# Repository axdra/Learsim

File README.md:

# Collection of Learsim code

## Glass cockpit displays

- **[`learsim-glass`](learsim-glass/)** — kiosk display app that hosts
  [glassout](https://glassout.flyingart.dev) views (and local standby/clock
  views) fullscreen. Runs headless on a Raspberry Pi and on Windows/macOS. One
  screen config per monitor, so two monitors on one Pi get two independent
  configs.
- **[`learsim-glass-admin`](learsim-glass-admin/)** — desktop app to configure,
  over the LAN, which view each glass screen shows.
- **[`learsim-glass-native`](learsim-glass-native/)** — a native (no-webview)
  display client that renders glassout panels directly via SDL2/KMSDRM. Much
  lighter on a Raspberry Pi than the webview build (no browser engine, no
  compositor) and speaks the same control API, so the admin manages it the same.

See each app's README for architecture, build, and headless-Pi setup.

## Other

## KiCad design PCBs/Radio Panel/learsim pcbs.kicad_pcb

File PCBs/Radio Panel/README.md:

# Learsim Radio Panel — PCB

KiCad project (`learsim pcbs.kicad_*`) for the Learsim flight-sim **COM/NAV radio
panel**: an ESP32-C6 drives two MAX7219 LED drivers that multiplex two 6-digit
7-segment displays, plus two rotary encoders, six mode buttons with per-button
SK6812 RGB backlights, two indicator LEDs and an SPDT toggle.

## Block diagram

```
         USB-C 5V ── Vbus ─┬─ ESP32-C6 (Vsys)
                           ├─ MAX7219 U2/U3  V+
                           └─ SK6812 D1..D6  VDD
 ESP32-C6 (U1)
   GPIO6  ── SPI DIN ─▶ U2.DIN ─▶ U2.DOUT ─▶ U3.DIN     (daisy-chain)
   GPIO7  ── SPI CLK ─▶ U2.CLK, U3.CLK
   GPIO4  ── SPI LOAD▶ U2.LOAD, U3.LOAD
   GPIO21 ── LED DATA▶ D5 ▶ D1 ▶ D2 ▶ D3 ▶ D4 ▶ D6      (WS2812-style chain)
   GPIO15/16/5  ── Encoder SW1 (MHz)  A / B / push
   GPIO18/19/20 ── Encoder SW2 (KHz)  A / B / push
   GPIO2/0/1/14 ── COM1 COM2 NAV1 Switch1 buttons
   EXIO2 / EXIO3 (TCA9554) ── NAV2 / ADF1 buttons
   GPIO3 / GPIO17 ── COM1 / COM2 indicator LEDs (D7 / D8)
   EXIO6 / EXIO7 (TCA9554) ── SW3 toggle throws A / B

   U2 ─▶ DS2 (6-digit display)      U3 ─▶ DS1 (6-digit display)
```

## ESP32-C6 GPIO map

| Function            | ESP32-C6 pin   | Net       |
|---------------------|----------------|-----------|
| MAX7219 SPI DIN     | GPIO6          | SPI_DIN   |
| MAX7219 SPI CLK     | GPIO7          | SPI_CLK   |
| MAX7219 SPI LOAD/CS | GPIO4          | SPI_LOAD  |
| SK6812 data out     | GPIO21         | LED_DIN   |
| Encoder MHz A / B   | GPIO15 / GPIO16 (TX) | ENC1_A/B |
| Encoder MHz push    | GPIO5          | ENC1_SW   |
| Encoder KHz A / B   | GPIO18 / GPIO19 | ENC2_A/B |
| Encoder KHz push    | GPIO20         | ENC2_SW   |
| COM1 button         | GPIO2          | BTN_COM1  |
| COM2 button         | GPIO0          | BTN_COM2  |
| NAV1 button         | GPIO1          | BTN_NAV1  |
| NAV2 button         | EXIO2 (TCA9554)| BTN_NAV2  |
| ADF1 button         | EXIO3 (TCA9554)| BTN_ADF1  |
| Switch1 button      | GPIO14         | BTN_Switch1 |
| COM1 indicator LED  | GPIO3          | COM1_LED  |
| COM2 indicator LED  | GPIO17 (RX)    | COM2_LED  |
| SW3 toggle throw 1  | EXIO6 (TCA9554)| SW3_A     |
| SW3 toggle throw 2  | EXIO7 (TCA9554)| SW3_B     |
| Power in            | USB-C (Vbus)   | +5V       |
| Logic rail          | 3V3            | +3V3      |

Spare pins for expansion: **GPIO8, GPIO9, EXIO1, EXIO4, EXIO5**. Note GPIO8/GPIO9
are ESP32-C6 strapping/boot pins (GPIO9 low at reset selects download mode) — only
attach loads there that are guaranteed high-or-floating at reset (GPIO8 also drives
the module's onboard RGB LED). **GPIO22/GPIO23 are NOT spare**: they are the I2C
bus (SDA/SCL) to the module's onboard TCA9554 expander that reads the NAV2/ADF1
buttons and SW3 — leave them unconnected; only I2C slaves may ever attach there.

**Encoder MHz B is on the TX pin (GPIO16) and the COM2 LED on RX (GPIO17)**, so
the UART0 serial console is not available; use the ESP32-C6's native USB for
flashing/logs. The ROM bootloader drives TX briefly at reset — harmless for the
encoder, but expect a short glitch on ENC1_B during boot.

**SW3 (SPDT toggle, 2MD1T1B1M2QES-5).** Common pole (pin 2) → GND; each throw read
with a 10 kΩ pull-up to +3V3 (pin 1 → EXIO6 via R15, pin 3 → EXIO7 via R16). A
throw reads LOW when selected and HIGH otherwise, so firmware can distinguish both
positions (and a centre-OFF state if the part has one). SW3 sits on the TCA9554
expander (EXIO6/EXIO7) specifically to keep it **off the GPIO8/GPIO9 strapping
pins** — an ON-ON toggle always grounds one throw, and GPIO9 held low at reset
would put the chip in download mode and stop the board booting. (ENC1_A remains on
GPIO15, also a strapping pin, but an idling encoder there is low-risk. The second
pole of SW3, pins 4–6, is unused.)

## SK6812 backlight chain

The RGB LEDs are reverse-mount SK6812MINI-E on the back of the board, shining
through cutouts under each Cherry-MX button. The data chain order follows board
position, **not** reference-designator order:

```
GPIO21 ▶ D5 (Switch1) ▶ D1 (COM1) ▶ D2 (COM2) ▶ D3 (NAV1) ▶ D4 (NAV2) ▶ D6 (ADF1)
```

Firmware must use this index order (0 = Switch1, 1 = COM1, … 5 = ADF1).

## MAX7219 ↔ display wiring (common-cathode)

Each MAX7219 drives one display. `U2 → DS2`, `U3 → DS1`. Segment lines are the
display **anodes**, digit lines are the **cathodes**.

| MAX7219 | Display pin | | MAX7219 | Display pin |
|---------|-------------|-|---------|-------------|
| SEG_A (14) | A (11) | | DIG0 (2)  | DIG1 (14) |
| SEG_B (16) | B (7)  | | DIG1 (11) | DIG2 (13) |
| SEG_C (20) | C (4)  | | DIG2 (6)  | DIG3 (12) |
| SEG_D (23) | D (1)  | | DIG3 (7)  | DIG4 (9)  |
| SEG_E (21) | E (3)  | | DIG4 (3)  | DIG5 (8)  |
| SEG_F (15) | F (10) | | DIG5 (10) | DIG6 (5)  |
| SEG_G (17) | G (6)  | | DIG6, DIG7 | *no-connect* (only 6 digits) |
| SEG_DP (22)| DP (2) | |         |             |

This matches the 6-digit display datasheet pinout (segments A=11, B=7, C=4, D=1,
E=3, F=10, G=6, DP=2; digits DIG1..6 = 14,13,12,9,8,5). Set the MAX7219 scan
limit to 6 digits in firmware.

## Supporting components

| Ref | Value | Purpose |
|-----|-------|---------|
| R1, R2 | 33 kΩ | MAX7219 ISET → V+ segment-current set (**required**) |
| R3–R8 | 10 kΩ | pull-ups for the six buttons (GPIO2/0/1/23/22/14) |
| R9–R14 | 10 kΩ | pull-ups on encoder A / B / push lines |
| R15, R16 | 10 kΩ | pull-ups on SW3 throws (EXIO6/EXIO7) |
| R17 | 150 Ω | COM1 indicator LED (D7) series resistor |
| R18 | 470 Ω | COM2 indicator LED (D8) series resistor — different value because D7/D8 are different LED colours |
| D7, D8 | 3 mm THT LED | COM1 / COM2 indicator LEDs |
| C1, C3 | 10 µF | MAX7219 V+ bulk decoupling |
| C2, C4 | 100 nF | MAX7219 V+ HF decoupling |
| C5 | 100 nF | ESP32 3V3 decoupling |
| C6 | 220 µF | +5V rail bulk reservoir |
| C7–C12 | 100 nF | one per SK6812 (VDD–VSS) |
| C13–C18 | 100 nF | RC debounce cap on each encoder A / B / push line |

**Encoder debounce:** each encoder A, B and push line has a 10 kΩ pull-up to +3V3
(R9–R14) and a 100 nF cap to GND (C13–C18), forming a ~1 ms RC low-pass that cleans
contact bounce in hardware. Buttons are debounced in firmware.

**Through-hole footprints (this iteration).** All added passives use THT footprints for
easy hand-assembly:

| Part | Footprint |
|------|-----------|
| R1–R18 | `Resistor_THT:R_Axial_DIN0207_L6.3mm_D2.5mm_P7.62mm_Horizontal` (1/4 W axial) |
| 100 nF (C2, C4, C5, C7–C18) | `Capacitor_THT:C_Disc_D5.0mm_W2.5mm_P5.00mm` (ceramic disc) |
| 10 µF (C1, C3) | `Capacitor_THT:CP_Radial_D5.0mm_P2.50mm` (electrolytic) |
| 220 µF (C6) | `Capacitor_THT:CP_Radial_D6.3mm_P2.50mm` (electrolytic) |
| D7, D8 | `LED_THT:LED_D3.0mm` |

The 10 µF / 220 µF caps (C1, C3, C6) are electrolytic and **polarized** — the terminal on
the `+5V` net is the **+** side. The SK6812 RGB LEDs remain SMD (no THT part exists).

## Design notes / to verify before fab

- **PCB reroute pending for SW3.** The schematic moves SW3_A/SW3_B from GPIO8/GPIO9
  (U1 pads 11/12) to EXIO6/EXIO7 (U1 pads 19/20). Run *Update PCB from Schematic*
  and reroute those two tracks, then re-run DRC.
- **3.3 V logic vs 5 V rails.** MAX7219 V+ and SK6812 VDD are at 5 V while the
  ESP32 drives 3.3 V logic. This usually works but is marginally out of MAX7219 VIH
  spec (3.5 V min); for robustness either run the MAX7219s / first SK6812 (D5) at
  ~4.3 V via a diode drop, or add a level shifter on DIN/CLK/LOAD and LED data.
- **+5 V trace width.** The +5 V distribution is currently routed at 0.2 mm while
  the board can draw several hundred mA (6× SK6812 up to ~60 mA each plus two
  MAX7219-driven displays). Widen the 5 V trunk to ≥1 mm or pour it, and consider a
  B.Cu GND pour (this also clears the DRC starved-thermal warnings on U3/SW1).
- **Powered from USB-C.** The board runs entirely off the ESP32-C6 module's USB-C;
  make sure the host/cable can supply the load, and consider capping SK6812
  brightness in firmware if the USB source is current-limited.
- **Encoder pinout.** EC12E2430803 is wired A/B = quadrature, C = common (GND),
  D/E = push switch. Confirm A/C pin identity against the specific part's datasheet.

## Verification status

Checked with KiCad 10 `kicad-cli` (ERC, DRC, netlist export):

- Schematic↔PCB parity clean before the SW3 pin move; SW3 reroute on the PCB is
  the one outstanding layout task (see above).
- ERC: remaining errors are the intentionally-spare pins (GPIO8/GPIO9, EXIO1–5,
  3V3_EN, RUN, MAX7219 DIG6/DIG7, U3 DOUT) plus missing-PWR_FLAG warnings on the
  +5V/+3V3 rails — all benign.
- DRC: 3 starved-thermal errors on the F.Cu GND pour (U3 GND pads, SW1 common);
  connectivity is intact via tracks, and a B.Cu GND pour would clear them.

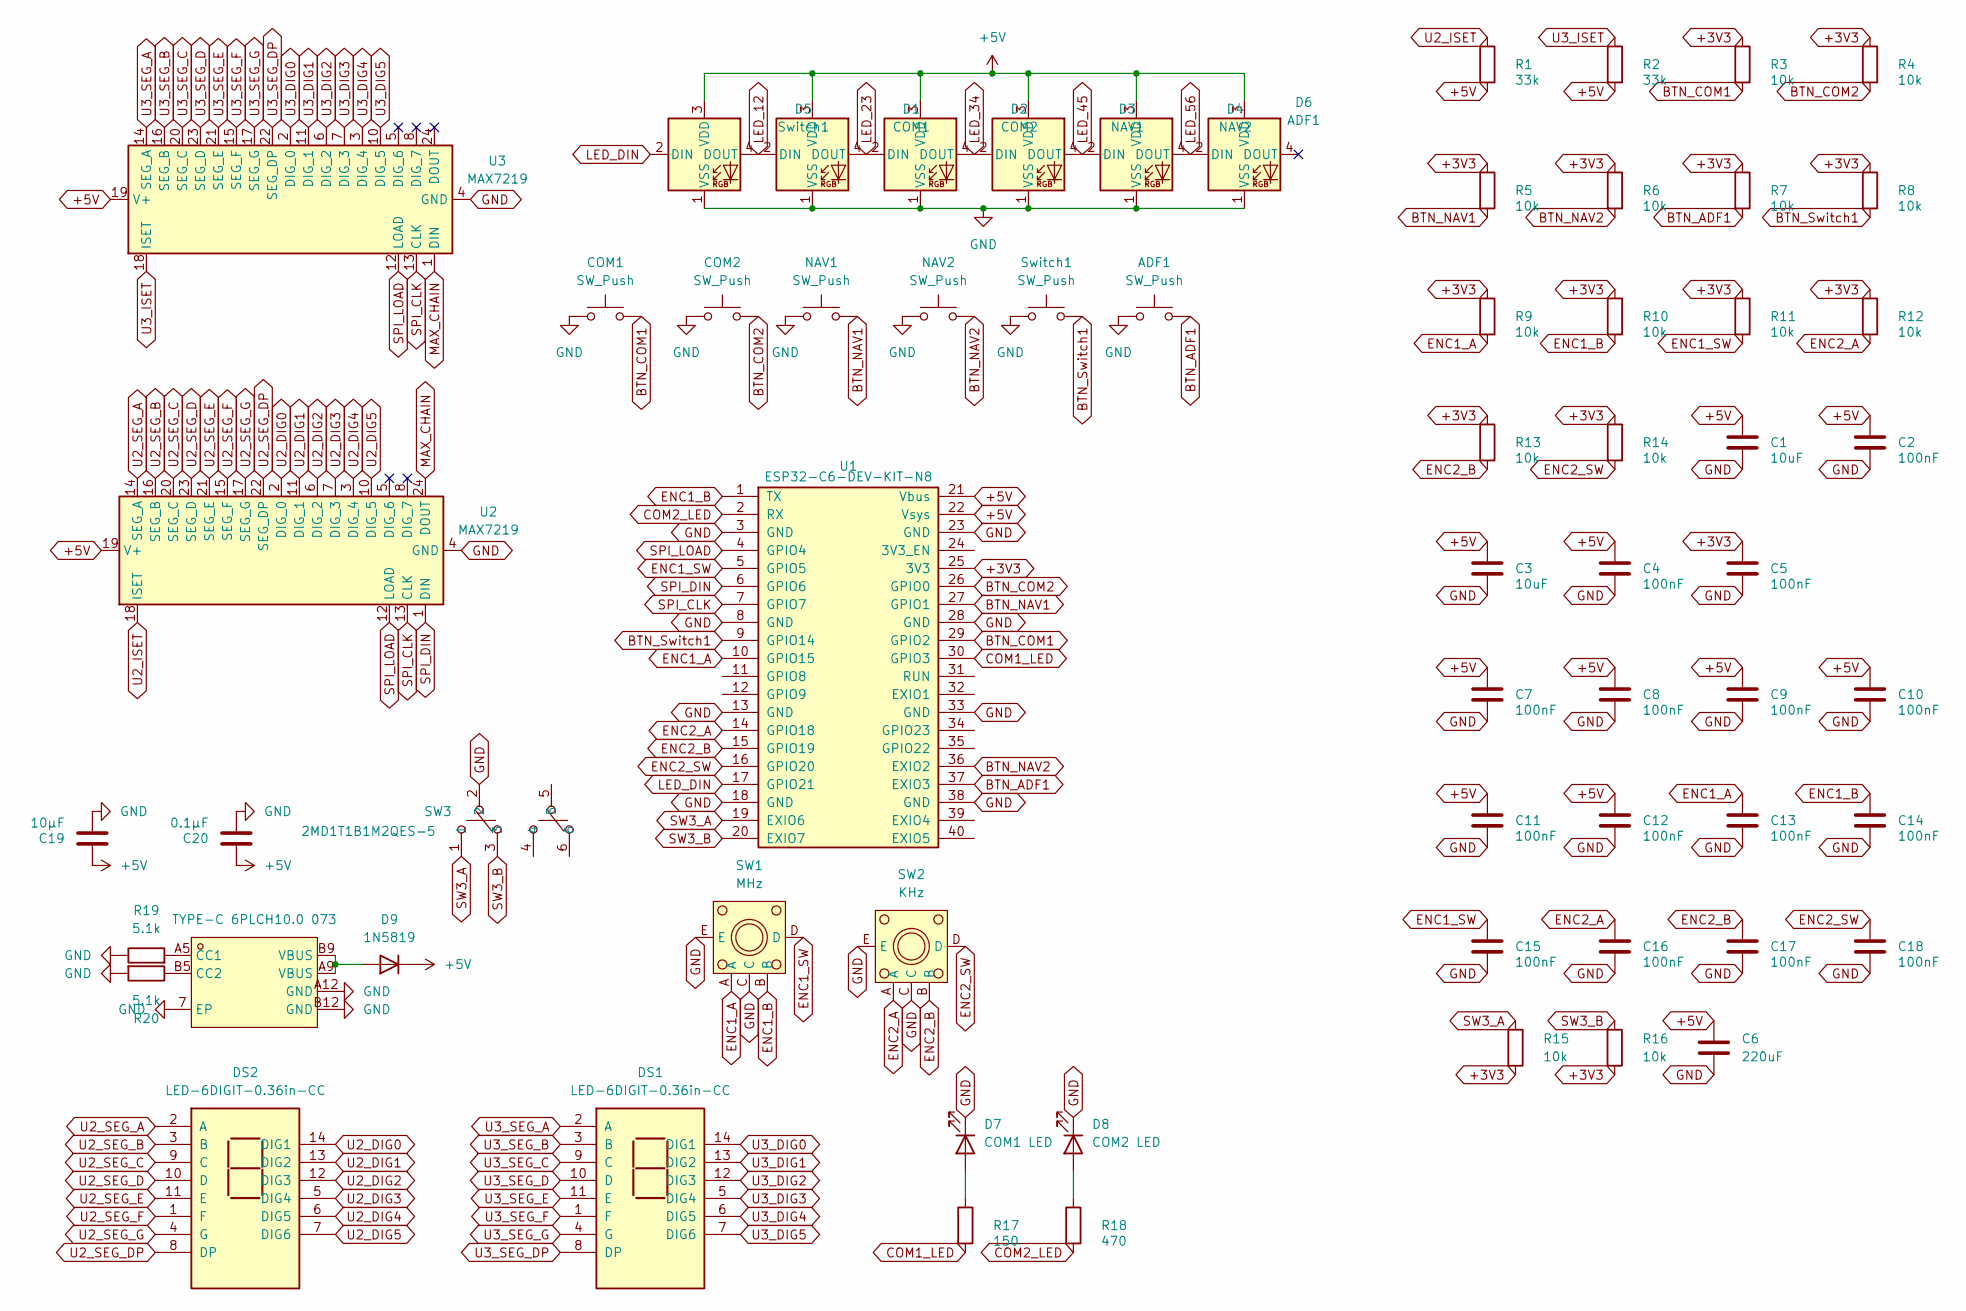
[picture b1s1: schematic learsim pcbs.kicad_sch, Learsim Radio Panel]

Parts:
ADF1: SW_Push; SW_Kailh_Choc_V2
C1, C3: 10uF; CP_Radial_D5.0mm_P2.50mm
C2, C4, C5, C7, C8, C9, C10, C11, C12, C13, C14, C15, C16, C17, C18: 100nF; C_Disc_D5.0mm_W2.5mm_P5.00mm
C6: 220uF; CP_Radial_D6.3mm_P2.50mm
C19: 10µF; C_Disc_D5.0mm_W2.5mm_P5.00mm
C20: 0.1µF; C_Disc_D5.0mm_W2.5mm_P5.00mm
COM1, COM2: SW_Push; SW_Kailh_Choc_V2
D1: COM1; LED_SK6812MINI-E_3.2x2.8mm_P1.5mm_ReverseMount
D2: COM2; LED_SK6812MINI-E_3.2x2.8mm_P1.5mm_ReverseMount
D3: NAV1; LED_SK6812MINI-E_3.2x2.8mm_P1.5mm_ReverseMount
D4: NAV2; LED_SK6812MINI-E_3.2x2.8mm_P1.5mm_ReverseMount
D5: Switch1; LED_SK6812MINI-E_3.2x2.8mm_P1.5mm_ReverseMount
D6: ADF1; LED_SK6812MINI-E_3.2x2.8mm_P1.5mm_ReverseMount
D7: COM1 LED; LED_D3.0mm
D8: COM2 LED; LED_D3.0mm
D9: 1N5819; D_DO-41_SOD81_P7.62mm_Horizontal; LCSC C110032
DS1, DS2: LED-6DIGIT-0.36in-CC; LED-6DIGIT-0.36in-CC_14P
NAV1, NAV2: SW_Push; SW_Kailh_Choc_V2
R1, R2: 33k; R_Axial_DIN0207_L6.3mm_D2.5mm_P7.62mm_Horizontal
R3, R4, R5, R6, R7, R8, R9, R10, R11, R12, R13, R14, R15, R16: 10k; R_Axial_DIN0207_L6.3mm_D2.5mm_P7.62mm_Horizontal
R17: 150; R_Axial_DIN0207_L6.3mm_D2.5mm_P7.62mm_Horizontal
R18: 470; R_Axial_DIN0207_L6.3mm_D2.5mm_P7.62mm_Horizontal
R19, R20: 5.1k; R_Axial_DIN0207_L6.3mm_D2.5mm_P7.62mm_Horizontal
SW1: MHz; SW-TH_EC12EXXXX; MPN EC12E2430803; LCSC Part C470684
SW2: KHz; SW-TH_EC12EXXXX; MPN EC12E2430803; LCSC Part C470684
SW3: 2MD1T1B1M2QES-5; SW-TH_2MD1T1B1M2QES-5; MPN 2MD1T1B1M2QES-5; LCSC Part C908282
Switch1: SW_Push; SW_Kailh_Choc_V2
U1: ESP32-C6-DEV-KIT-N8; ESP32-C6-Pico; MPN ESP32-C6-DEV-KIT-N8
U2, U3: MAX7219; DIP-24_W7.62mm
U4: TYPE-C 6PLCH10.0 073; USB-C-TH_TYPE-C-6PLCH10.0-073; MPN TYPE-C 6PLCH10.0 073; LCSC Part C5156601

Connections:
+3V3: C5.1, R3.1, R4.1, R5.1, R6.1, R7.1, R8.1, R9.1, R10.1, R11.1, R12.1, R13.1, R14.1, R15.2, R16.2, U1.25 (3V3)
+5V: C1.1, C2.1, C3.1, C4.1, C6.1, C7.1, C8.1, C9.1, C10.1, C11.1, C12.1, C19.1, C20.1, D1.3 (VDD), D2.3 (VDD), D3.3 (VDD), D4.3 (VDD), D5.3 (VDD), D6.3 (VDD), D9.1 (K), R1.2, R2.2, U1.21 (Vbus), U1.22 (Vsys), U2.19 (V+), U3.19 (V+)
BTN_ADF1: ADF1.2, R7.2, U1.37 (EXIO3)
BTN_COM1: COM1.2, R3.2, U1.29 (GPIO2)
BTN_COM2: COM2.2, R4.2, U1.26 (GPIO0)
BTN_NAV1: NAV1.2, R5.2, U1.27 (GPIO1)
BTN_NAV2: NAV2.2, R6.2, U1.36 (EXIO2)
BTN_Switch1: R8.2, Switch1.2, U1.9 (GPIO14)
COM1_LED: R17.2, U1.30 (GPIO3)
COM2_LED: R18.2, U1.2 (RX)
ENC1_A: C13.1, R9.2, SW1.A, U1.10 (GPIO15)
ENC1_B: C14.1, R10.2, SW1.B, U1.1 (TX)
ENC1_SW: C15.1, R11.2, SW1.D, U1.5 (GPIO5)
ENC2_A: C16.1, R12.2, SW2.A, U1.14 (GPIO18)
ENC2_B: C17.1, R13.2, SW2.B, U1.15 (GPIO19)
ENC2_SW: C18.1, R14.2, SW2.D, U1.16 (GPIO20)
GND: ADF1.1, C1.2, C2.2, C3.2, C4.2, C5.2, C6.2, C7.2, C8.2, C9.2, C10.2, C11.2, C12.2, C13.2, C14.2, C15.2, C16.2, C17.2, C18.2, C19.2, C20.2, COM1.1, COM2.1, D1.1 (VSS), D2.1 (VSS), D3.1 (VSS), D4.1 (VSS), D5.1 (VSS), D6.1 (VSS), D7.1 (K), D8.1 (K), NAV1.1, NAV2.1, R19.1, R20.2, SW1.C, SW1.E, SW2.C, SW2.E, SW3.2, Switch1.1, U1.3 (GND), U1.8 (GND), U1.13 (GND), U1.18 (GND), U1.23 (GND), U1.28 (GND), U1.33 (GND), U1.38 (GND), U2.4 (GND), U2.9 (GND), U3.4 (GND), U3.9 (GND), U4.7 (EP), U4.A12 (GND), U4.B12 (GND)
LED_12: D1.2 (DIN), D5.4 (DOUT)
LED_23: D1.4 (DOUT), D2.2 (DIN)
LED_34: D2.4 (DOUT), D3.2 (DIN)
LED_45: D3.4 (DOUT), D4.2 (DIN)
LED_56: D4.4 (DOUT), D6.2 (DIN)
LED_DIN: D5.2 (DIN), U1.17 (GPIO21)
MAX_CHAIN: U2.24 (DOUT), U3.1 (DIN)
unnamed: D7.2 (A), R17.1
unnamed: D8.2 (A), R18.1
unnamed: D9.2 (A), U4.A9 (VBUS), U4.B9 (VBUS)
unnamed: R19.2, U4.A5 (CC1)
unnamed: R20.1, U4.B5 (CC2)
SPI_CLK: U1.7 (GPIO7), U2.13 (CLK), U3.13 (CLK)
SPI_DIN: U1.6 (GPIO6), U2.1 (DIN)
SPI_LOAD: U1.4 (GPIO4), U2.12 (LOAD), U3.12 (LOAD)
SW3_A: R15.1, SW3.1, U1.19 (EXIO6)
SW3_B: R16.1, SW3.3, U1.20 (EXIO7)
U2_DIG0: DS2.14 (DIG1), U2.2 (DIG_0)
U2_DIG1: DS2.13 (DIG2), U2.11 (DIG_1)
U2_DIG2: DS2.12 (DIG3), U2.6 (DIG_2)
U2_DIG3: DS2.5 (DIG4), U2.7 (DIG_3)
U2_DIG4: DS2.6 (DIG5), U2.3 (DIG_4)
U2_DIG5: DS2.7 (DIG6), U2.10 (DIG_5)
U2_ISET: R1.1, U2.18 (ISET)
U2_SEG_A: DS2.2 (A), U2.14 (SEG_A)
U2_SEG_B: DS2.3 (B), U2.16 (SEG_B)
U2_SEG_C: DS2.9 (C), U2.20 (SEG_C)
U2_SEG_D: DS2.10 (D), U2.23 (SEG_D)
U2_SEG_DP: DS2.8 (DP), U2.22 (SEG_DP)
U2_SEG_E: DS2.11 (E), U2.21 (SEG_E)
U2_SEG_F: DS2.1 (F), U2.15 (SEG_F)
U2_SEG_G: DS2.4 (G), U2.17 (SEG_G)
U3_DIG0: DS1.14 (DIG1), U3.2 (DIG_0)
U3_DIG1: DS1.13 (DIG2), U3.11 (DIG_1)
U3_DIG2: DS1.12 (DIG3), U3.6 (DIG_2)
U3_DIG3: DS1.5 (DIG4), U3.7 (DIG_3)
U3_DIG4: DS1.6 (DIG5), U3.3 (DIG_4)
U3_DIG5: DS1.7 (DIG6), U3.10 (DIG_5)
U3_ISET: R2.1, U3.18 (ISET)
U3_SEG_A: DS1.2 (A), U3.14 (SEG_A)
U3_SEG_B: DS1.3 (B), U3.16 (SEG_B)
U3_SEG_C: DS1.9 (C), U3.20 (SEG_C)
U3_SEG_D: DS1.10 (D), U3.23 (SEG_D)
U3_SEG_DP: DS1.8 (DP), U3.22 (SEG_DP)
U3_SEG_E: DS1.11 (E), U3.21 (SEG_E)
U3_SEG_F: DS1.1 (F), U3.15 (SEG_F)
U3_SEG_G: DS1.4 (G), U3.17 (SEG_G)

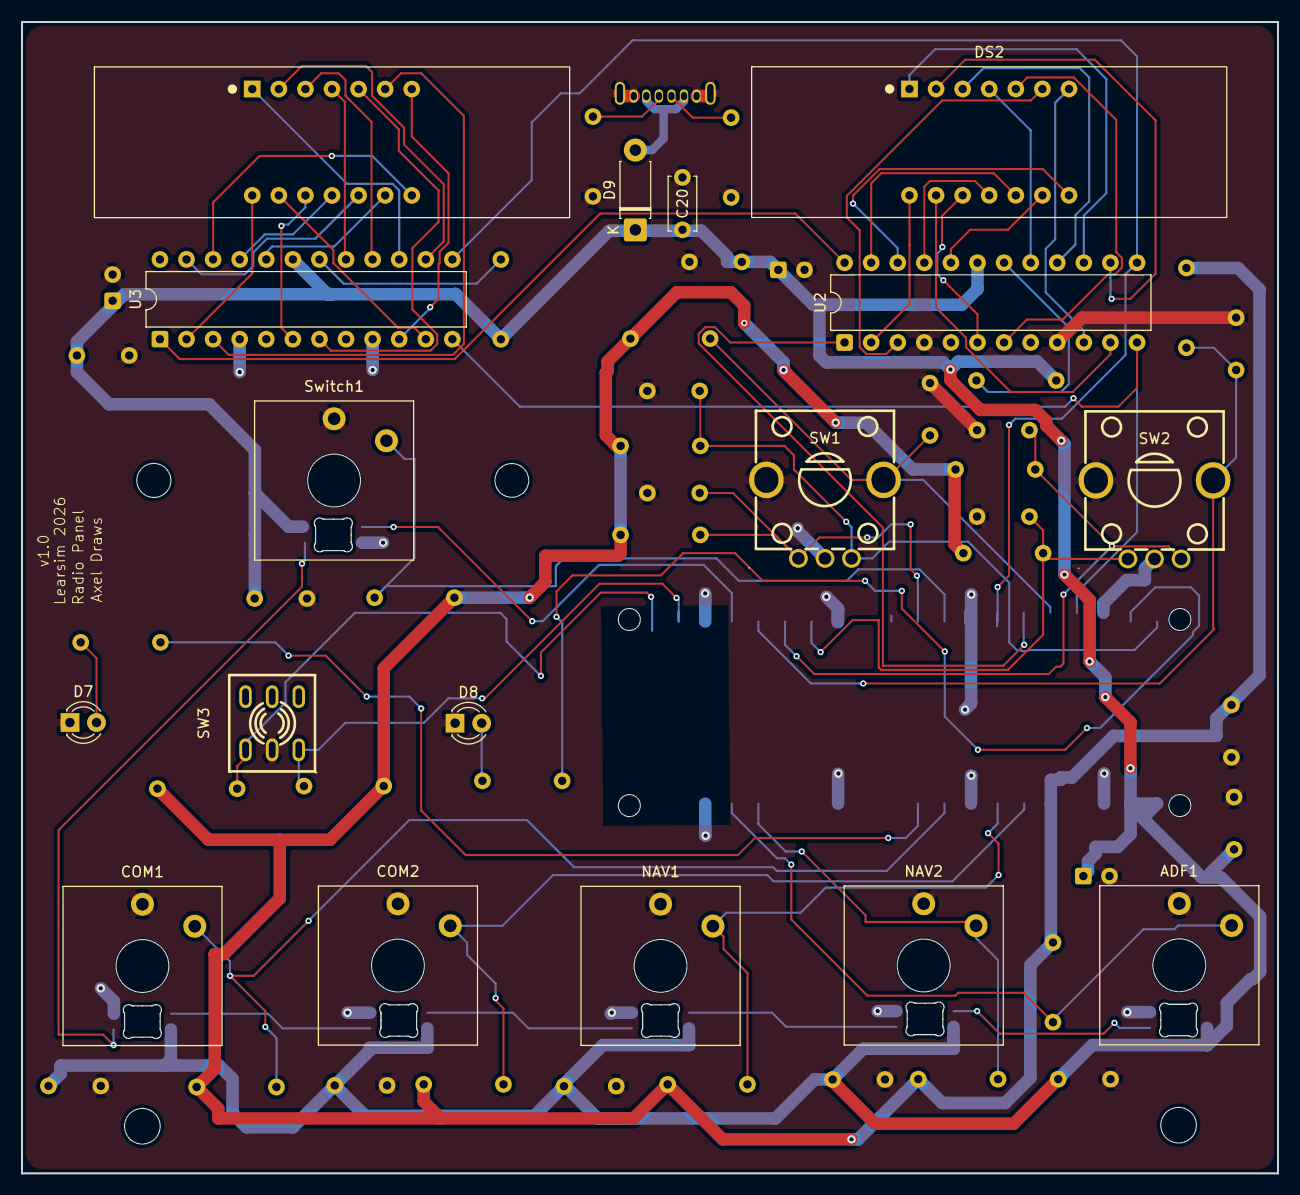
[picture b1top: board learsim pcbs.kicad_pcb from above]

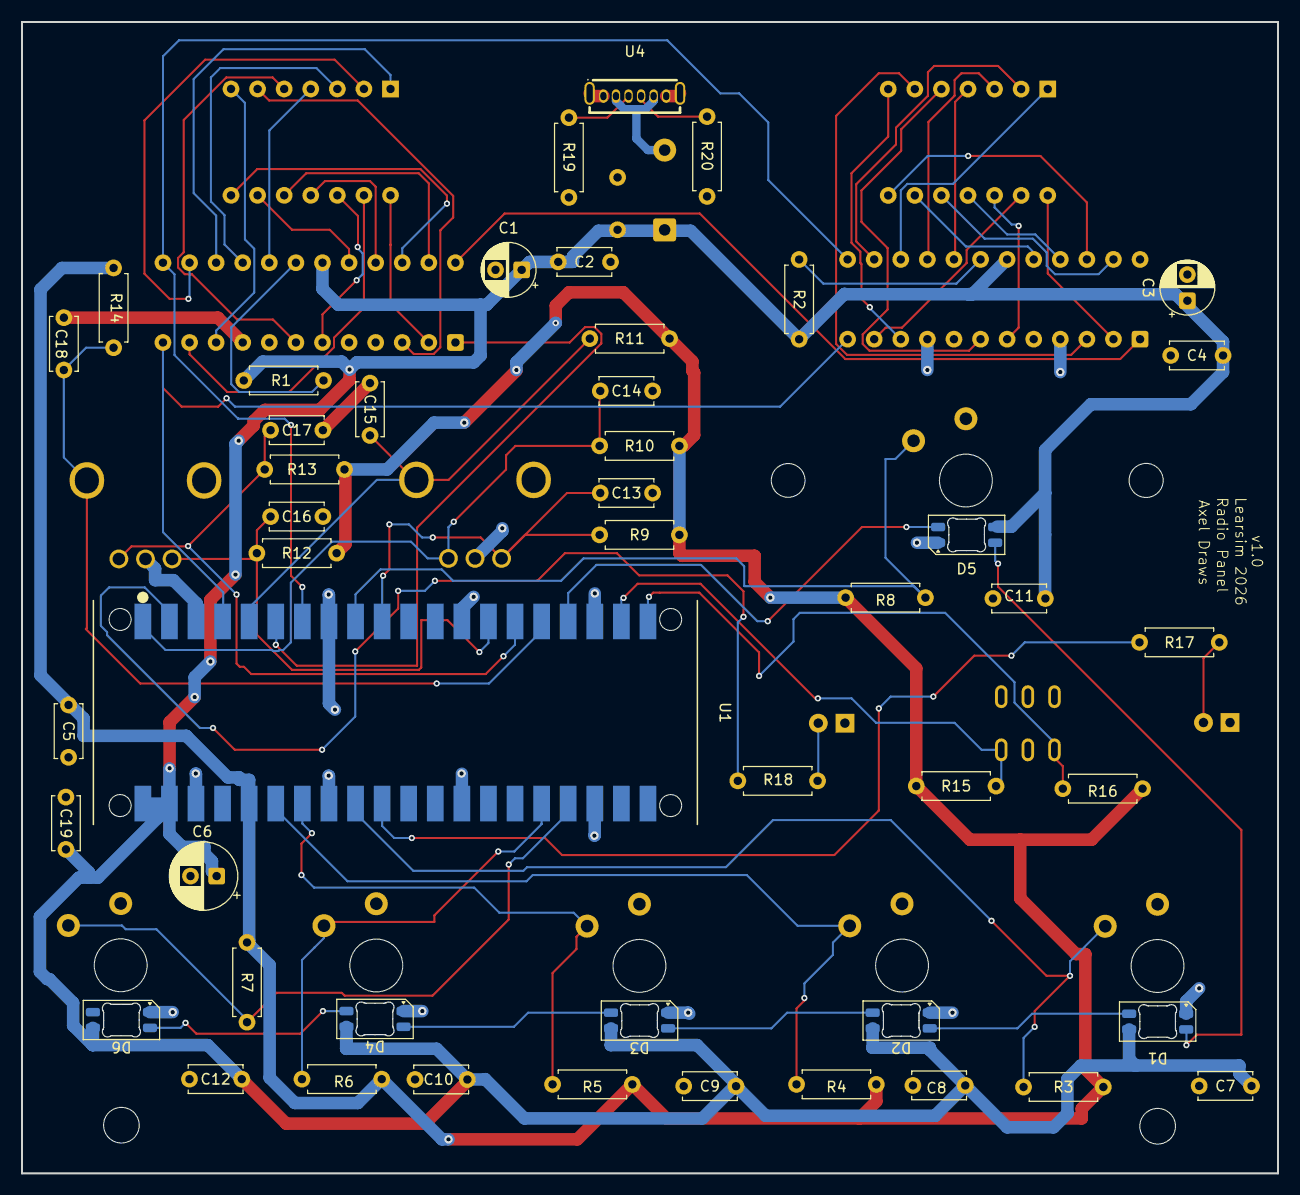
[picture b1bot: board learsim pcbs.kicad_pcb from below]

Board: 2 copper layers, 120.0 x 110.0 mm, 64 parts (47 on the bottom side), 64 nets.

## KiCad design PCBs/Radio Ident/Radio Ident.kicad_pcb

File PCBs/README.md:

# Learsim Radio Panel — PCB

KiCad project (`learsim pcbs.kicad_*`) for the Learsim flight-sim **COM/NAV radio
panel**: an ESP32-C6 drives two MAX7219 LED drivers that multiplex two 6-digit
7-segment displays, plus two rotary encoders, six mode buttons with per-button
SK6812 RGB backlights, two indicator LEDs and an SPDT toggle.

## Block diagram

```
         USB-C 5V ── Vbus ─┬─ ESP32-C6 (Vsys)
                           ├─ MAX7219 U2/U3  V+
                           └─ SK6812 D1..D6  VDD
 ESP32-C6 (U1)
   GPIO6  ── SPI DIN ─▶ U2.DIN ─▶ U2.DOUT ─▶ U3.DIN     (daisy-chain)
   GPIO7  ── SPI CLK ─▶ U2.CLK, U3.CLK
   GPIO4  ── SPI LOAD▶ U2.LOAD, U3.LOAD
   GPIO21 ── LED DATA▶ D5 ▶ D1 ▶ D2 ▶ D3 ▶ D4 ▶ D6      (WS2812-style chain)
   GPIO15/16/5  ── Encoder SW1 (MHz)  A / B / push
   GPIO18/19/20 ── Encoder SW2 (KHz)  A / B / push
   GPIO2/0/1/23/22/14 ── COM1 COM2 NAV1 NAV2 ADF1 Switch1 buttons
   GPIO3 / GPIO17 ── COM1 / COM2 indicator LEDs (D7 / D8)
   EXIO6 / EXIO7 (TCA9554) ── SW3 toggle throws A / B

   U2 ─▶ DS2 (6-digit display)      U3 ─▶ DS1 (6-digit display)
```

## ESP32-C6 GPIO map

| Function            | ESP32-C6 pin   | Net       |
|---------------------|----------------|-----------|
| MAX7219 SPI DIN     | GPIO6          | SPI_DIN   |
| MAX7219 SPI CLK     | GPIO7          | SPI_CLK   |
| MAX7219 SPI LOAD/CS | GPIO4          | SPI_LOAD  |
| SK6812 data out     | GPIO21         | LED_DIN   |
| Encoder MHz A / B   | GPIO15 / GPIO16 (TX) | ENC1_A/B |
| Encoder MHz push    | GPIO5          | ENC1_SW   |
| Encoder KHz A / B   | GPIO18 / GPIO19 | ENC2_A/B |
| Encoder KHz push    | GPIO20         | ENC2_SW   |
| COM1 button         | GPIO2          | BTN_COM1  |
| COM2 button         | GPIO0          | BTN_COM2  |
| NAV1 button         | GPIO1          | BTN_NAV1  |
| NAV2 button         | GPIO23         | BTN_NAV2  |
| ADF1 button         | GPIO22         | BTN_ADF1  |
| Switch1 button      | GPIO14         | BTN_Switch1 |
| COM1 indicator LED  | GPIO3          | COM1_LED  |
| COM2 indicator LED  | GPIO17 (RX)    | COM2_LED  |
| SW3 toggle throw 1  | EXIO6 (TCA9554)| SW3_A     |
| SW3 toggle throw 2  | EXIO7 (TCA9554)| SW3_B     |
| Power in            | USB-C (Vbus)   | +5V       |
| Logic rail          | 3V3            | +3V3      |

Spare pins for expansion: **GPIO8, GPIO9, EXIO1–EXIO5**. Note GPIO8/GPIO9 are
ESP32-C6 strapping/boot pins (GPIO9 low at reset selects download mode) — only
attach loads there that are guaranteed high-or-floating at reset.

**Encoder MHz B is on the TX pin (GPIO16) and the COM2 LED on RX (GPIO17)**, so
the UART0 serial console is not available; use the ESP32-C6's native USB for
flashing/logs. The ROM bootloader drives TX briefly at reset — harmless for the
encoder, but expect a short glitch on ENC1_B during boot.

**SW3 (SPDT toggle, 2MD1T1B1M2QES-5).** Common pole (pin 2) → GND; each throw read
with a 10 kΩ pull-up to +3V3 (pin 1 → EXIO6 via R15, pin 3 → EXIO7 via R16). A
throw reads LOW when selected and HIGH otherwise, so firmware can distinguish both
positions (and a centre-OFF state if the part has one). SW3 sits on the TCA9554
expander (EXIO6/EXIO7) specifically to keep it **off the GPIO8/GPIO9 strapping
pins** — an ON-ON toggle always grounds one throw, and GPIO9 held low at reset
would put the chip in download mode and stop the board booting. (ENC1_A remains on
GPIO15, also a strapping pin, but an idling encoder there is low-risk. The second
pole of SW3, pins 4–6, is unused.)

## SK6812 backlight chain

The RGB LEDs are reverse-mount SK6812MINI-E on the back of the board, shining
through cutouts under each Cherry-MX button. The data chain order follows board
position, **not** reference-designator order:

```
GPIO21 ▶ D5 (Switch1) ▶ D1 (COM1) ▶ D2 (COM2) ▶ D3 (NAV1) ▶ D4 (NAV2) ▶ D6 (ADF1)
```

Firmware must use this index order (0 = Switch1, 1 = COM1, … 5 = ADF1).

## MAX7219 ↔ display wiring (common-cathode)

Each MAX7219 drives one display. `U2 → DS2`, `U3 → DS1`. Segment lines are the
display **anodes**, digit lines are the **cathodes**.

| MAX7219 | Display pin | | MAX7219 | Display pin |
|---------|-------------|-|---------|-------------|
| SEG_A (14) | A (11) | | DIG0 (2)  | DIG1 (14) |
| SEG_B (16) | B (7)  | | DIG1 (11) | DIG2 (13) |
| SEG_C (20) | C (4)  | | DIG2 (6)  | DIG3 (12) |
| SEG_D (23) | D (1)  | | DIG3 (7)  | DIG4 (9)  |
| SEG_E (21) | E (3)  | | DIG4 (3)  | DIG5 (8)  |
| SEG_F (15) | F (10) | | DIG5 (10) | DIG6 (5)  |
| SEG_G (17) | G (6)  | | DIG6, DIG7 | *no-connect* (only 6 digits) |
| SEG_DP (22)| DP (2) | |         |             |

This matches the 6-digit display datasheet pinout (segments A=11, B=7, C=4, D=1,
E=3, F=10, G=6, DP=2; digits DIG1..6 = 14,13,12,9,8,5). Set the MAX7219 scan
limit to 6 digits in firmware.

## Supporting components

| Ref | Value | Purpose |
|-----|-------|---------|
| R1, R2 | 33 kΩ | MAX7219 ISET → V+ segment-current set (**required**) |
| R3–R8 | 10 kΩ | pull-ups for the six buttons (GPIO2/0/1/23/22/14) |
| R9–R14 | 10 kΩ | pull-ups on encoder A / B / push lines |
| R15, R16 | 10 kΩ | pull-ups on SW3 throws (EXIO6/EXIO7) |
| R17 | 150 Ω | COM1 indicator LED (D7) series resistor |
| R18 | 470 Ω | COM2 indicator LED (D8) series resistor — different value because D7/D8 are different LED colours |
| D7, D8 | 3 mm THT LED | COM1 / COM2 indicator LEDs |
| C1, C3 | 10 µF | MAX7219 V+ bulk decoupling |
| C2, C4 | 100 nF | MAX7219 V+ HF decoupling |
| C5 | 100 nF | ESP32 3V3 decoupling |
| C6 | 220 µF | +5V rail bulk reservoir |
| C7–C12 | 100 nF | one per SK6812 (VDD–VSS) |
| C13–C18 | 100 nF | RC debounce cap on each encoder A / B / push line |

**Encoder debounce:** each encoder A, B and push line has a 10 kΩ pull-up to +3V3
(R9–R14) and a 100 nF cap to GND (C13–C18), forming a ~1 ms RC low-pass that cleans
contact bounce in hardware. Buttons are debounced in firmware.

**Through-hole footprints (this iteration).** All added passives use THT footprints for
easy hand-assembly:

| Part | Footprint |
|------|-----------|
| R1–R18 | `Resistor_THT:R_Axial_DIN0207_L6.3mm_D2.5mm_P7.62mm_Horizontal` (1/4 W axial) |
| 100 nF (C2, C4, C5, C7–C18) | `Capacitor_THT:C_Disc_D5.0mm_W2.5mm_P5.00mm` (ceramic disc) |
| 10 µF (C1, C3) | `Capacitor_THT:CP_Radial_D5.0mm_P2.50mm` (electrolytic) |
| 220 µF (C6) | `Capacitor_THT:CP_Radial_D6.3mm_P2.50mm` (electrolytic) |
| D7, D8 | `LED_THT:LED_D3.0mm` |

The 10 µF / 220 µF caps (C1, C3, C6) are electrolytic and **polarized** — the terminal on
the `+5V` net is the **+** side. The SK6812 RGB LEDs remain SMD (no THT part exists).

## Design notes / to verify before fab

- **PCB reroute pending for SW3.** The schematic moves SW3_A/SW3_B from GPIO8/GPIO9
  (U1 pads 11/12) to EXIO6/EXIO7 (U1 pads 19/20). Run *Update PCB from Schematic*
  and reroute those two tracks, then re-run DRC.
- **3.3 V logic vs 5 V rails.** MAX7219 V+ and SK6812 VDD are at 5 V while the
  ESP32 drives 3.3 V logic. This usually works but is marginally out of MAX7219 VIH
  spec (3.5 V min); for robustness either run the MAX7219s / first SK6812 (D5) at
  ~4.3 V via a diode drop, or add a level shifter on DIN/CLK/LOAD and LED data.
- **+5 V trace width.** The +5 V distribution is currently routed at 0.2 mm while
  the board can draw several hundred mA (6× SK6812 up to ~60 mA each plus two
  MAX7219-driven displays). Widen the 5 V trunk to ≥1 mm or pour it, and consider a
  B.Cu GND pour (this also clears the DRC starved-thermal warnings on U3/SW1).
- **Powered from USB-C.** The board runs entirely off the ESP32-C6 module's USB-C;
  make sure the host/cable can supply the load, and consider capping SK6812
  brightness in firmware if the USB source is current-limited.
- **Encoder pinout.** EC12E2430803 is wired A/B = quadrature, C = common (GND),
  D/E = push switch. Confirm A/C pin identity against the specific part's datasheet.

## Verification status

Checked with KiCad 10 `kicad-cli` (ERC, DRC, netlist export):

- Schematic↔PCB parity clean before the SW3 pin move; SW3 reroute on the PCB is
  the one outstanding layout task (see above).
- ERC: remaining errors are the intentionally-spare pins (GPIO8/GPIO9, EXIO1–5,
  3V3_EN, RUN, MAX7219 DIG6/DIG7, U3 DOUT) plus missing-PWR_FLAG warnings on the
  +5V/+3V3 rails — all benign.
- DRC: 3 starved-thermal errors on the F.Cu GND pour (U3 GND pads, SW1 common);
  connectivity is intact via tracks, and a B.Cu GND pour would clear them.

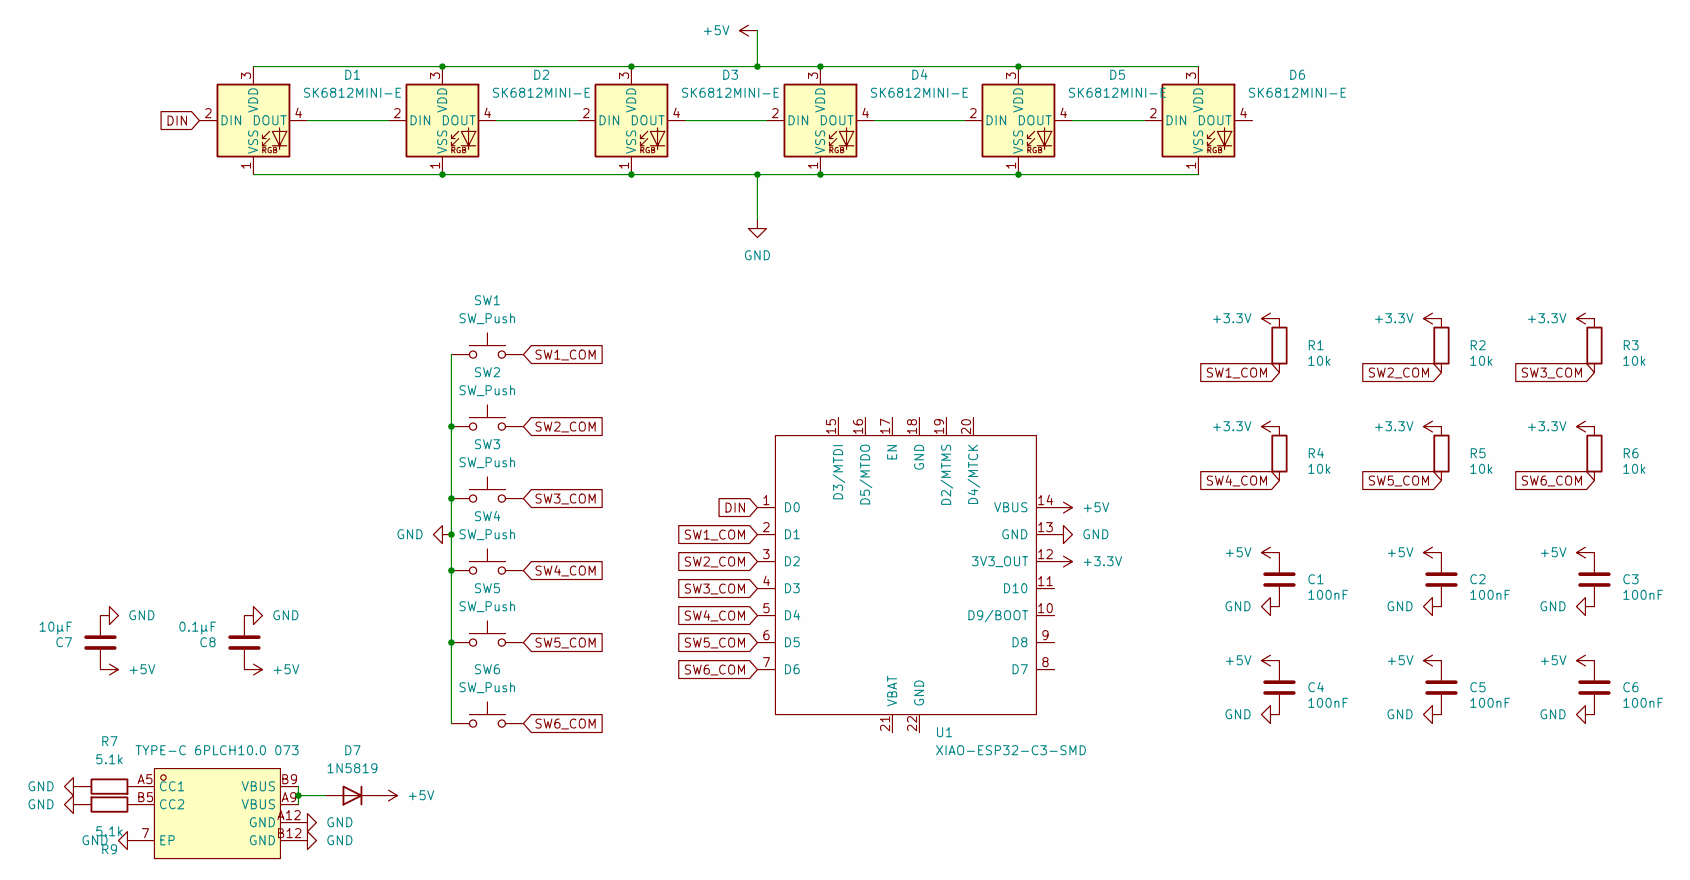
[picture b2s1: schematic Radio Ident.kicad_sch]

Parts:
C1, C2, C3, C4, C5, C6: 100nF; C_Disc_D5.0mm_W2.5mm_P5.00mm
C7: 10µF; C_Disc_D5.0mm_W2.5mm_P5.00mm
C8: 0.1µF; C_Disc_D5.0mm_W2.5mm_P5.00mm
D1, D2, D3, D4, D5, D6: SK6812MINI-E; LED_SK6812MINI-E_3.2x2.8mm_P1.5mm_ReverseMount
D7: 1N5819; D_DO-41_SOD81_P7.62mm_Horizontal; LCSC C110032
R1, R2, R3, R4, R5, R6: 10k; R_Axial_DIN0207_L6.3mm_D2.5mm_P7.62mm_Horizontal
R7, R9: 5.1k; R_Axial_DIN0207_L6.3mm_D2.5mm_P7.62mm_Horizontal
SW1, SW2, SW3, SW4, SW5, SW6: SW_Push; SW_Kailh_Choc_V2
U1: XIAO-ESP32-C3-SMD
U3: TYPE-C 6PLCH10.0 073; USB-C-TH_TYPE-C-6PLCH10.0-073; MPN TYPE-C 6PLCH10.0 073; LCSC Part C5156601

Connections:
+3.3V: R1.1, R2.1, R3.1, R4.1, R5.1, R6.1, U1.12 (3V3_OUT)
+5V: C1.1, C2.1, C3.1, C4.1, C5.1, C6.1, C7.1, C8.1, D1.3 (VDD), D2.3 (VDD), D3.3 (VDD), D4.3 (VDD), D5.3 (VDD), D6.3 (VDD), D7.1 (K), U1.14 (VBUS)
DIN: D1.2 (DIN), U1.1 (D0)
GND: C1.2, C2.2, C3.2, C4.2, C5.2, C6.2, C7.2, C8.2, D1.1 (VSS), D2.1 (VSS), D3.1 (VSS), D4.1 (VSS), D5.1 (VSS), D6.1 (VSS), R7.1, R9.2, SW1.1, SW2.1, SW3.1, SW4.1, SW5.1, SW6.1, U1.13 (GND), U3.7 (EP), U3.A12 (GND), U3.B12 (GND)
unnamed: D1.4 (DOUT), D2.2 (DIN)
unnamed: D2.4 (DOUT), D3.2 (DIN)
unnamed: D3.4 (DOUT), D4.2 (DIN)
unnamed: D4.4 (DOUT), D5.2 (DIN)
unnamed: D5.4 (DOUT), D6.2 (DIN)
unnamed: D7.2 (A), U3.A9 (VBUS), U3.B9 (VBUS)
unnamed: R7.2, U3.A5 (CC1)
unnamed: R9.1, U3.B5 (CC2)
SW1_COM: R1.2, SW1.2, U1.2 (D1)
SW2_COM: R2.2, SW2.2, U1.3 (D2)
SW3_COM: R3.2, SW3.2, U1.4 (D3)
SW4_COM: R4.2, SW4.2, U1.5 (D4)
SW5_COM: R5.2, SW5.2, U1.6 (D5)
SW6_COM: R6.2, SW6.2, U1.7 (D6)

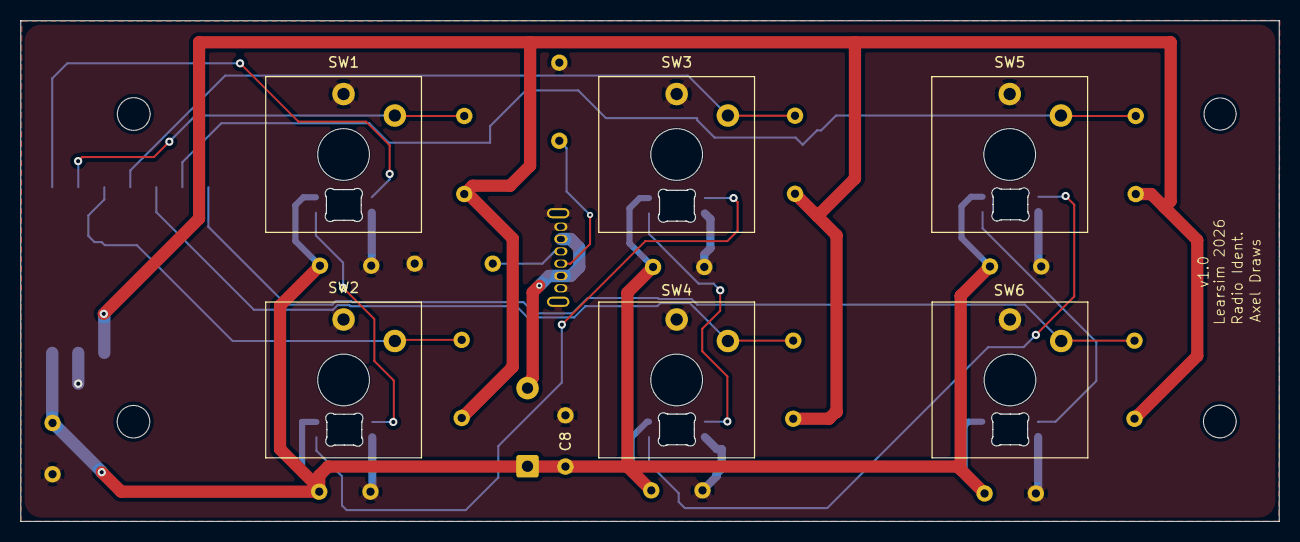
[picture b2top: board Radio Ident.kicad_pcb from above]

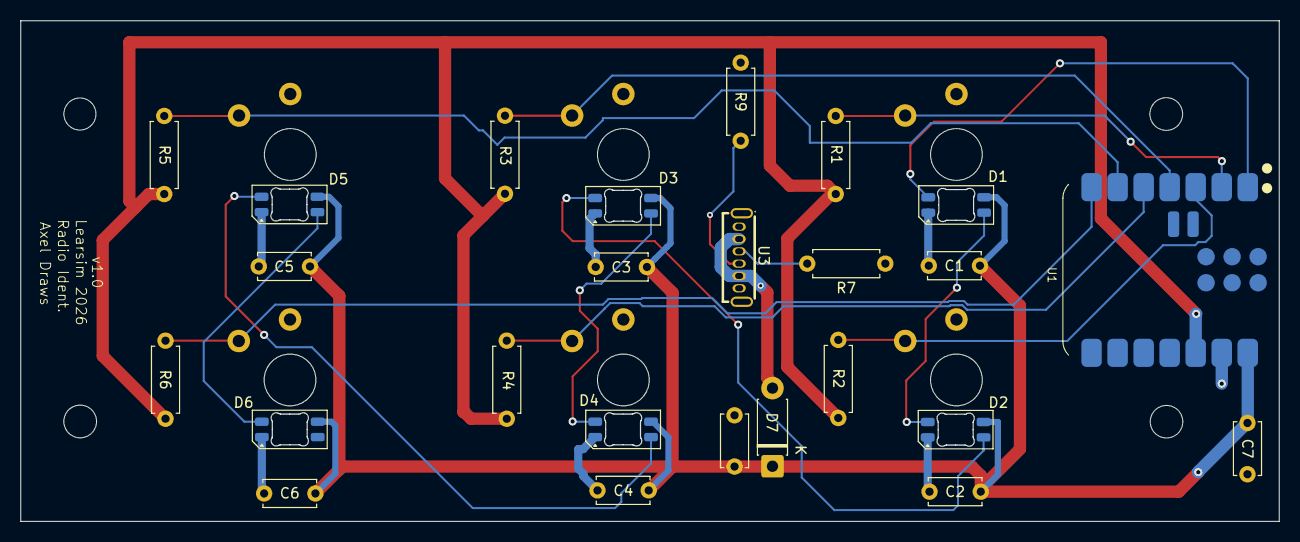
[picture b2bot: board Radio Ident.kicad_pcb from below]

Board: 2 copper layers, 122.8 x 48.8 mm, 31 parts (25 on the bottom side), 18 nets.

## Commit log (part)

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2020-10-25 renamed: .vscode/launch.json -> instrumentsetupscript/.vscode/launch.json
2020-10-30 "AutoTest.py" is now reading memory and doing everything
2020-10-31 Fixed so when FS is quit it drops the mem reading
2020-11-07 Added Multithreading, not working atm
2020-11-07 Added purple icon
2020-11-08 Moved repo and changed README
2020-11-08 Changed ReadMe
2020-12-13 Python script for enabling touch screens
    Python script for enabling touch screens for instruments poped out. Pretty crude way.
2020-12-14 Moved into own directory
